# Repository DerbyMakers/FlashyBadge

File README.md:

# FlashyBadge
Badge circuit board for learning to solder

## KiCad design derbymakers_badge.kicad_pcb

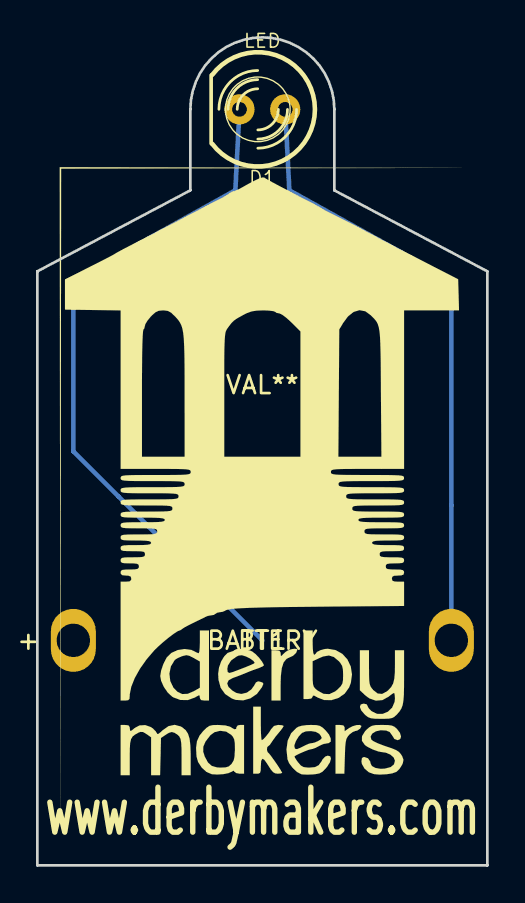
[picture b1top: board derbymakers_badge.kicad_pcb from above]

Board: 2 copper layers, 25.0 x 46.0 mm, 3 parts (0 on the bottom side), 2 nets.

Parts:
BT1: BATTERY; CR2032_CLIP_BACK
BadgePin-20mm: VAL**; BadgePin-20mm
D1: LED; LED-5MM

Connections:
unnamed: BT1.1, D1.1
unnamed: BT1.2, D1.2

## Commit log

2015-02-05 initial add of kicad project files and gerber, ps, svg board files
